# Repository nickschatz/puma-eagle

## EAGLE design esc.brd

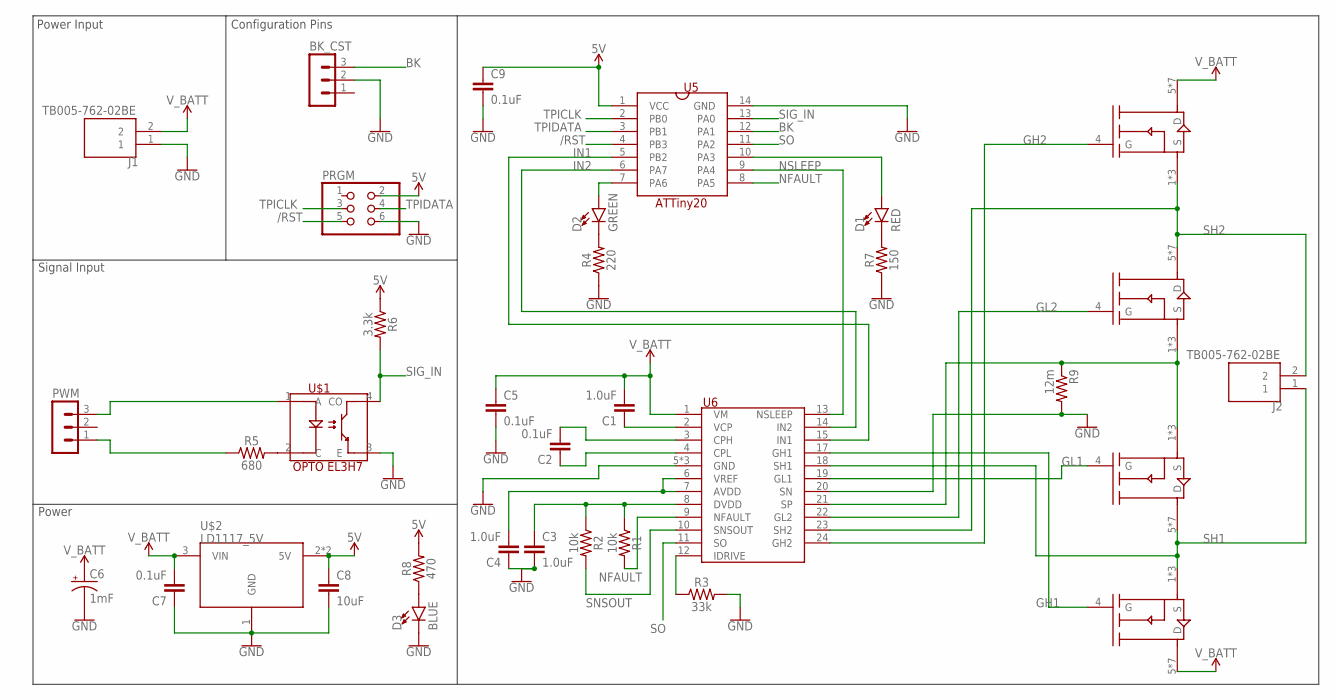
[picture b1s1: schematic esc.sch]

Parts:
BK_CST: MA03-1
C1, C3, C4: 1.0uF; 0603
C2, C5, C7, C9: 0.1uF; 0603
C6: 1mF; CPOL-RADIAL-5MM-10MM
C8: 10uF; 0603
D1: RED; LED-0603
D2: GREEN; LED-0603
D3: BLUE; LED-0603
J1, J2: TB005-762-02BE; CUI_TB005-762-02BE
PRGM: PINHD-2X3; 2X03
PWM: MA03-1
R1, R2: 10k; 0603
R3: 33k; 0603
R4: 220; 0603
R5: 680; 0603
R6: 3.3k; 0603
R7: 150; 0603
R8: 470; 0603
R9: 12m; R2512
U1, U2, U3, U4: AON6558; POWER-SO8
U5: ATTINY20; SOIC127P599X265-14
U6: DRV8701; QFN50P400X400X100-25T280
U$1: EL3H7; SOIC127P700X265-4
U$2: LD1117_5V; SOT223

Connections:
5V: C8.1, C9.1, PRGM.2, R6.1, R8.2, U5.1 (VCC), U$2.2 (5V), U$2.4 (5V)
/RST: PRGM.5, U5.4 (PB3)
BK: BK_CST.3, U5.12 (PA1)
GH1: U4.4 (G), U6.17 (GH1)
GH2: U1.4 (G), U6.24 (GH2)
GL1: U3.4 (G), U6.19 (GL1)
GL2: U2.4 (G), U6.22 (GL2)
GND: BK_CST.2, C3.2, C4.1, C5.2, C6.-, C7.1, C8.2, C9.2, D3.C, J1.1, PRGM.6, R3.2, R4.1, R7.1, R9.2, U5.14 (GND), U6.5 (GND), U6.16 (GND), U6.20 (SN), U6.25 (GND), U$1.3 (E), U$2.1 (GND)
IN: PWM.3, U$1.1 (A)
IN1: U5.5 (PB2), U6.15 (IN1)
IN2: U5.6 (PA7), U6.14 (IN2)
IN_GND: PWM.1, R5.1
unnamed: C1.1, U6.2 (VCP)
unnamed: C2.2, U6.3 (CPH)
unnamed: C2.1, U6.4 (CPL)
unnamed: D2.A, U5.7 (PA6)
unnamed: C3.1, R1.1, R2.1, U6.8 (DVDD)
unnamed: R3.1, U6.12 (IDRIVE)
unnamed: C4.2, U6.6 (VREF), U6.7 (AVDD)
unnamed: D1.A, U5.10 (PA3)
unnamed: R5.2, U$1.2 (C)
unnamed: R9.1, U2.1 (S), U2.2 (S), U2.3 (S), U3.1 (S), U3.2 (S), U3.3 (S), U6.21 (SP)
unnamed: D2.C, R4.2
unnamed: D1.C, R7.2
unnamed: D3.A, R8.1
NFAULT: R1.2, U5.8 (PA5), U6.9 (NFAULT)
NSLEEP: U5.9 (PA4), U6.13 (NSLEEP)
SH1: J2.1, U3.5 (D), U3.6 (D), U3.7 (D), U3.8 (D), U3.PAD (D), U3.SIDEPAD1 (D), U3.SIDEPAD2 (D), U4.1 (S), U4.2 (S), U4.3 (S), U6.18 (SH1)
SH2: J2.2, U1.1 (S), U1.2 (S), U1.3 (S), U2.5 (D), U2.6 (D), U2.7 (D), U2.8 (D), U2.PAD (D), U2.SIDEPAD1 (D), U2.SIDEPAD2 (D), U6.23 (SH2)
SIG_IN: R6.2, U5.13 (PA0), U$1.4 (CO)
SNSOUT: R2.2, U6.10 (SNSOUT)
SO: U5.11 (PA2), U6.11 (SO)
TPICLK: PRGM.3, U5.2 (PB0)
TPIDATA: PRGM.4, U5.3 (PB1)
V_BATT: C1.2, C5.1, C6.+, C7.2, J1.2, U1.5 (D), U1.6 (D), U1.7 (D), U1.8 (D), U1.PAD (D), U1.SIDEPAD1 (D), U1.SIDEPAD2 (D), U4.5 (D), U4.6 (D), U4.7 (D), U4.8 (D), U4.PAD (D), U4.SIDEPAD1 (D), U4.SIDEPAD2 (D), U6.1 (VM), U$2.3 (VIN)

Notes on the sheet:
Configuration Pins
Power
Power Input
Signal Input

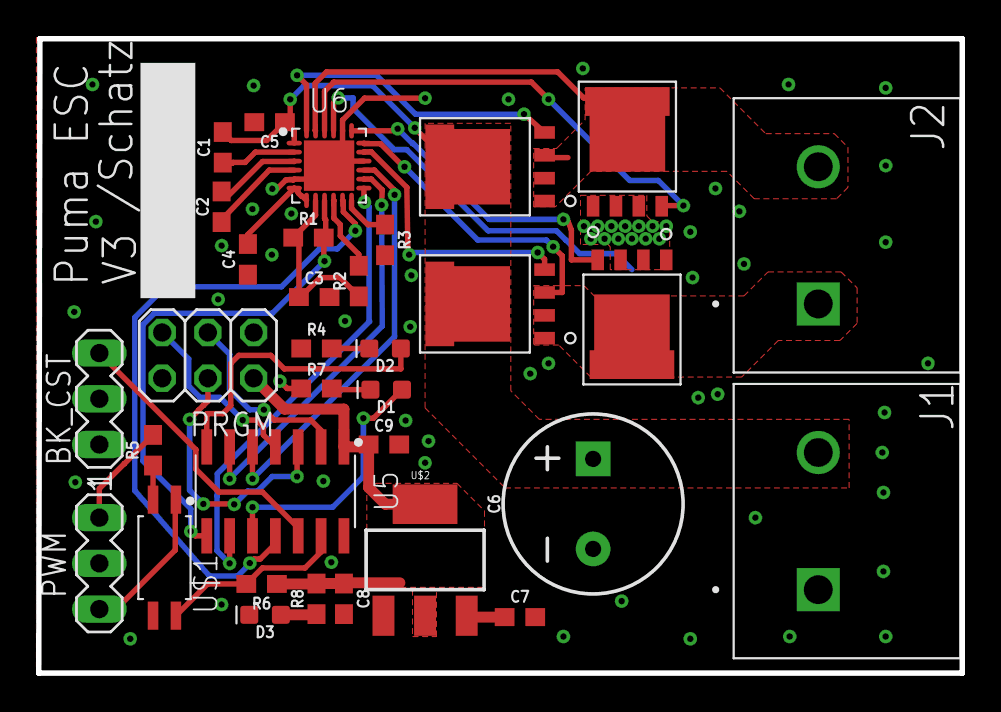
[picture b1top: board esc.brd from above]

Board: 2 copper layers, 51.3 x 35.2 mm, 34 parts (1 on the bottom side), 35 nets.

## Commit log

2019-01-26 Initial commit. V2 of board, first produced version.
2019-09-15 Update to board v3
    New power connectors and compactify layout
2019-09-22 Add current sense features
2019-09-22 Minor via placement changes

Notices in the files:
parts and their libraries:
SparkFun-Capacitors: Licensing: Creative Commons ShareAlike 4.0 International - https://creativecommons.org/licenses/by-sa/4.0
